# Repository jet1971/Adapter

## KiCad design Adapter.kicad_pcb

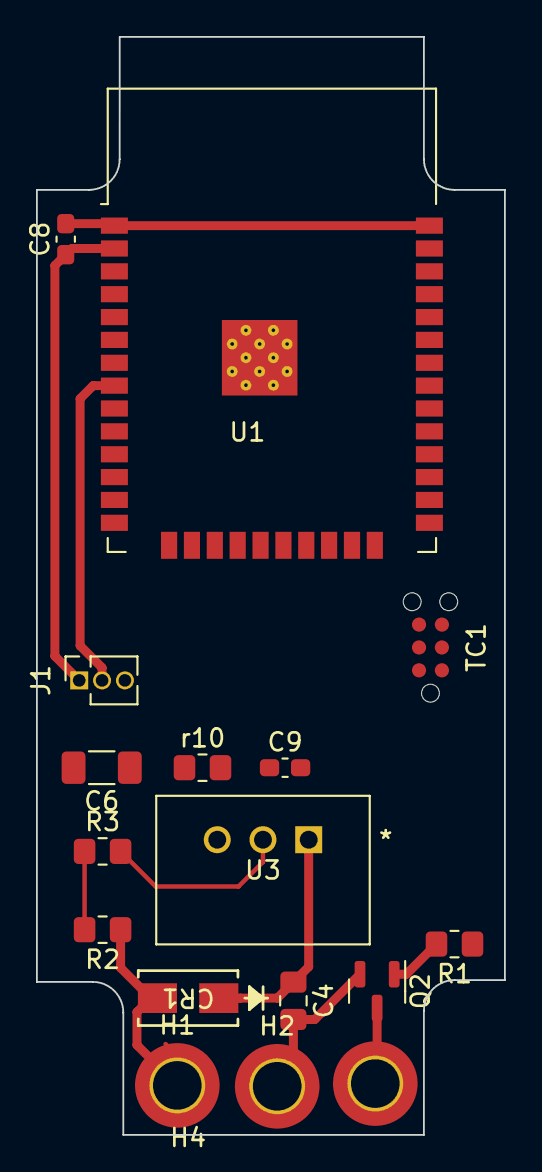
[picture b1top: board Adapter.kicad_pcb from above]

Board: 2 copper layers, 26.0 x 61.0 mm, 17 parts (0 on the bottom side), 13 nets.

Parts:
C4: 10uf/50v; C_0805_2012Metric_Pad1.18x1.45mm_HandSolder
C6: 22uF/10v; C_1206_3216Metric_Pad1.33x1.80mm_HandSolder
C8, C9: 100n; C_0603_1608Metric_Pad1.08x0.95mm_HandSolder
CR1: RS1G-E3/61T; DIODE_DO214AC
H1: 12 Volt +; MountingHole_2.7mm_M2.5_DIN965_Pad_TopBottom
H2: GND; MountingHole_2.7mm_M2.5_DIN965_Pad_TopBottom
H4: Output; MountingHole_2.7mm_M2.5_DIN965_Pad_TopBottom
J1: Conn_01x03_Socket; PinSocket_1x03_P1.27mm_Vertical
Q2: BC846; SOT-23
R1: 1K; R_0805_2012Metric_Pad1.20x1.40mm_HandSolder
R2: 100k; R_0805_2012Metric_Pad1.20x1.40mm_HandSolder
R3: 16k; R_0805_2012Metric_Pad1.20x1.40mm_HandSolder
TC1: TC2030-IDC; TC2030-IDC-NL
U1: ESP32-WROOM-32D; ESP32-WROOM-32
U3: K7803M-1000R3
r10: 10k; R_0805_2012Metric_Pad1.20x1.40mm_HandSolder

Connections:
+3.3 Volt: C6.1, C8.1, J1.1, TC1.2, U1.2 (VDD), U3.3 (+VO/GND), r10.1
+ 12 Volt: CR1.2, H1.1, R2.1
/Power/+12 Volt: C4.1, CR1.1, U3.1 (VIN)
EN: C9.1, TC1.1, U1.3 (EN), r10.2
GND: C4.2, C6.2, C8.2, C9.2, H2.1, J1.3, Q2.2 (E), R3.2, TC1.4, U1.1 (GND), U1.15 (GND), U1.38 (GND), U3.2 (GND/-VO)
IO0: TC1.6, U1.25 (IO0)
unnamed: J1.2, U1.8 (IO32)
unnamed: Q2.1 (B), R1.2
unnamed: H4.1, Q2.3 (C)
unnamed: R1.1, U1.16 (IO13)
unnamed: R2.2, R3.1, U1.9 (IO33)
RX: TC1.5, U1.34 (RXD0/IO3)
TX: TC1.3, U1.35 (TXD0/IO1)

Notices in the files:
parts and their libraries:
Copyright 2021 Accelerated Designs. All rights reserved.
